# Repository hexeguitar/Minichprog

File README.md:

# Minichprog
### ESP32-S2 based programmer/debugger for the WCH CH32V003 series MCU.  
  
Hardware compatible with CNLohr's ESP32-S2 ch32v003 programmer:  
https://github.com/cnlohr/cnhardware/tree/master/esp32s2-funprog  
Firmware and flashing instructions availble here:  
https://github.com/cnlohr/esp32s2-cookbook/tree/master/ch32v003programmer

Differences:
- 500mA polyfuse on the VBUS rail
- USB protection IC
- Current limited power switches
- 5V and 3.3V present led indicators
- smaller footprint, fits into the "USB dongle" 
  acrylic enclosure (same as original WCHLinkE)
- U.FL connector for external WiFI antenna

PCB is 4 layer, designed using KiCAD7. Gerbers in ZIP file are included as well as HTML BOM.  

--- 
Pictures below show rev A, which had additional target discharge option. It was not necessary since the BL2555 power switches have that feature built in.

---  
PCB is designed to fit into one of those transparent "USB" enclosures, the same the original WCHLinkE programmer is using.  

------
(c) 06.2023 by Piotr Zapart  
www.hexefx.com

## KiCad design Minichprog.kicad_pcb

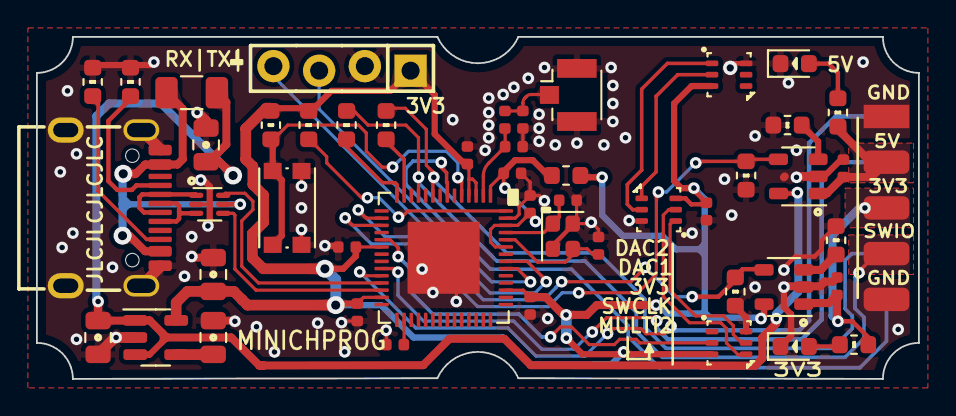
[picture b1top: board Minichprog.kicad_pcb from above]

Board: 4 copper layers, 49.0 x 19.0 mm, 50 parts (1 on the bottom side), 41 nets.

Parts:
AE1: Antenna_Shield; U.FL_Hirose_U.FL-R-SMT-1_Vertical
C2: 1u; Hx_C_0805_2012Metric
C3, C4, C5: 10p; Hx_C_0402_1005Metric
C6: 1n; Hx_C_0805_2012Metric
C7, C8, C10, C11, C12, C13, C14, C15, C16, C18: 1u; Hx_C_0402_1005Metric
C9, C17: 10u; Hx_C_0805_2012Metric
C19: DNP; Hx_C_0402_1005Metric
D1, D2, D3: WS2816C-2121; WS2816-2121
D4: 0603_BLUE; LED_0603_1608Metric
D5: 0603_PINK; LED_0603_1608Metric
F1: 500mA; Fuse_1206_3216Metric
FB1: 1k100M; L_0603_1608Metric
J1: USB_C_Receptacle_USB2.0_TYPE_C_31_M_12; USB_C_TYPE-C-31-M-12
J2, J4: Conn_01x05; PinHeader_1x05_P2.54mm_SMDpads
J3: Conn_01x04; 1x4_254_offset
L1: 6.8nH; L_0402_1005Metric
R2, R3, R4, R9: 5k1; Hx_R_0603_1608Metric
R5, R6, R7, R8, R10, R11: 10k; Hx_R_0603_1608Metric
R12, R13: 82k; Hx_R_0603_1608Metric
SW1: SW_Push; SW_Push_1P1T_NO_CK_KMR2
U1: RT9193-33GB; SOT-23-5
U2: NUF2042XV6T1G; SOT-563
U3: ESP32-S2; QFN-56-1EP_7x7mm_P0.4mm_EP4x4mm
U4, U5: BL2555; SOT-23-5
Y1: 40MHz; Crystal_SMD_2016-4Pin_2.0x1.6mm

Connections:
+3.3VP: C15.2, J2.3, J4.3, R9.1, U4.1 (OUT)
+3V3: C9.2, C10.2, C11.2, C13.2, C14.2, C18.1, D1.3 (V), D2.3 (V), D3.3 (V), FB1.2, J3.1, R2.2, R5.2, U1.5 (VOUT), U3.3 (VDD3P3), U3.4 (VDD3P3), U3.20 (V333P3_RTC), U3.27 (VDD3P3_RTC_IO), U3.45 (VDD3P3_CPU), U4.5 (IN)
+5V: C2.2, C17.2, F1.2, U1.1 (VIN), U1.3 (ON/~OFF), U5.5 (IN)
+5VP: C16.2, J2.2, R8.1, U5.1 (OUT)
/CHIP_PU: R2.1, U3.56 (CHIP_PU)
/DAC1: J4.2, U3.23 (DAC1|GPIO17)
/DAC2: J4.1, U3.24 (DAC2|GPIO18)
/LED_DATA: D1.2 (DI), U3.19 (GPIO14)
/MULTI2: J4.5, U3.7 (GPIO2)
/SWCLK: J4.4, R6.1, U3.9 (GPIO4)
/SWCLK_PU: R6.2, U3.13 (GPIO8)
/SWIO: J2.4, R7.1, U3.11 (GPIO6)
/SWIO_PU: R7.2, U3.14 (GPIO9)
/UART_RX: J3.4, U3.49 (GPIO44|U0RXD)
/UART_TX: J3.3, U3.48 (GPIO43|U0TXD)
/USB_DN: U2.6 (D1O), U3.25 (USB_DN|GPIO19)
/USB_DP: U2.4 (D2O), U3.26 (USB_DP|GPIO20)
/USB_N: J1.A7 (D-), J1.B7 (D-), U2.1 (D1I)
/USB_P: J1.A6 (D+), J1.B6 (D+), U2.3 (D2I)
/VDD3V3_EN: R10.1, U3.16 (GPIO11), U4.4 (EN)
/VDD5_EN: R11.1, U3.17 (GPIO12), U5.4 (EN)
GND: AE1.2 (Shield), C2.1, C3.2, C4.2, C5.2, C6.1, C7.2, C8.2, C9.1, C10.1, C11.1, C12.1, C13.1, C14.1, C15.1, C16.1, C17.1, C18.2, C19.2, D1.6 (G), D2.6 (G), D3.6 (G), D4.1 (K), D5.1 (K), J1.A1B12 (GND), J1.A12B1 (GND), J1.SH (SHIELD), J2.1, J2.5, J3.2, R3.2, R4.2, R10.2, R11.2, R12.2, R13.2, SW1.2, U1.2 (GND), U2.2 (GND), U3.55 (GPIO46), U3.57 (GND), U4.2 (GND), U5.2 (GND), Y1.2, Y1.4
unnamed: AE1.1 (A), C19.1, L1.1
unnamed: D1.5 (BO), D2.1 (BI)
unnamed: D1.4 (DO), D2.2 (DI)
unnamed: D2.5 (BO), D3.1 (BI)
unnamed: D2.4 (DO), D3.2 (DI)
unnamed: D4.2 (A), R8.2
unnamed: D5.2 (A), R9.2
unnamed: J1.A5 (CC1), R3.1
unnamed: J1.B5 (CC2), R4.1
unnamed: C6.2, U1.4 (BP)
unnamed: R5.1, SW1.1, U3.5 (GPIO0)
unnamed: C5.1, L1.2, U3.2 (LNA_IN)
unnamed: C12.2, U3.30 (VDD_SPI)
unnamed: C3.1, U3.52 (XTAL_N), Y1.3
unnamed: C4.1, U3.53 (XTAL_P), Y1.1
unnamed: R12.1, U4.3 (SET)
unnamed: R13.1, U5.3 (SET)
VBUS: F1.1, J1.A4B9 (VBUS), J1.A9B4 (VBUS), U2.5 (VBUS)
VDDA: C7.1, C8.1, FB1.1, U3.1 (VDDA), U3.51 (VDDA), U3.54 (VDDA)
